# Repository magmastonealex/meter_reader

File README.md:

meter_reader
====

This is an open-hardware design for a magnetic gas / water meter "reader" or "snooper". It contains a magnetometer and microcontroller, and can measure the rotations of a water meter or oscillations of the bellows in a gas meter to fairly accurately track consumption of both natural gas and water.

The device communicates externally using CAN, accepting configuration and reporting sensor values.

Schematics and PCB design are in the root of this repository. I have built a few devices, but would not consider the hardware to be "fully qualified" yet - I still need to do some transient testing and measure power supplies and signal integrity. I'd also still like to find a more available magnetometer - MLX3094RLD is _barely_ available and a bit annoying to solder.

Firmware in `firmware/` is Rust code targetting the MSPM0G3107 on the board. I _think_ this is the first working example of MSPM0 CAN access in Rust on the internet :) It requires modifications to the mspm0-data crate which I have in a branch here: https://github.com/magmastonealex/mspm0-data - there is an open PR upstream where smarter people than I are figuring out a better way to do this.

The firmware right now is just bringing up various peripherals to prove they work - the code is very, very ugly, requiring a lot of cleanup, and doesn't really "do" anything yet.

More to come, including a blog post detailing assembly, development, and setup

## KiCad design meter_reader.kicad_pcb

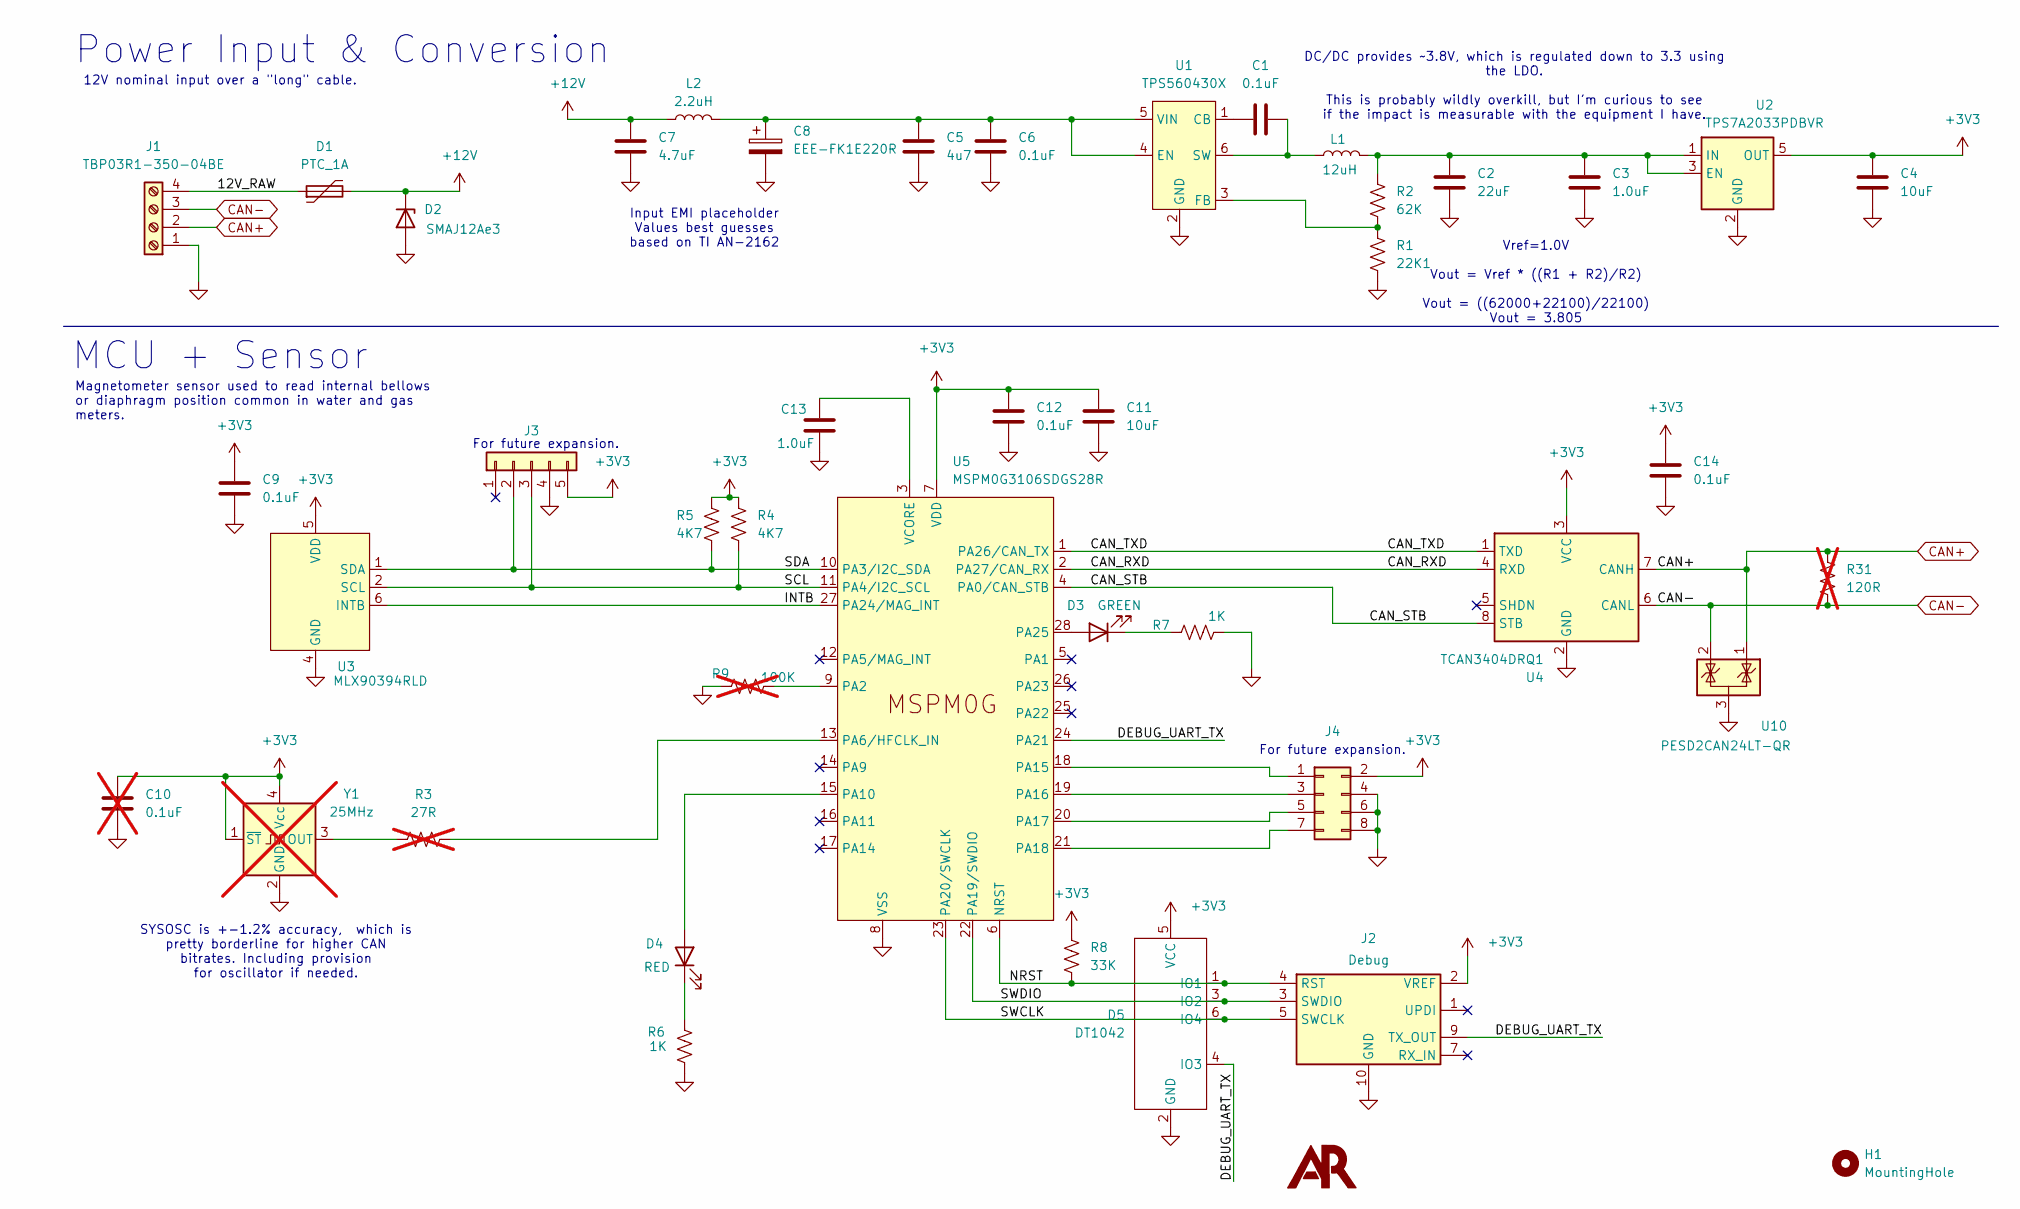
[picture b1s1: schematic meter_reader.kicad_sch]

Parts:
C1, C9: 0.1uF; C_0402_1005Metric
C2: 22uF; C_0805_2012Metric_Pad1.18x1.45mm_HandSolder
C3, C13: 1.0uF; C_0805_2012Metric_Pad1.18x1.45mm_HandSolder
C4, C11: 10uF; C_0805_2012Metric_Pad1.18x1.45mm_HandSolder
C5: 4u7; C_1206_3216Metric
C6, C12, C14: 0.1uF; C_0805_2012Metric_Pad1.18x1.45mm_HandSolder
C7: 4.7uF; C_1206_3216Metric
C8: EEE-FK1E220R; CP_Elec_5x5.8
C10: 0.1uF; C_0805_2012Metric_Pad1.18x1.45mm_HandSolder; not fitted
D1: PTC_1A; Fuse_1812
D2: SMAJ12Ae3; D_SMA
D3: GREEN; LED_0805_2012Metric_Pad1.15x1.40mm_HandSolder
D4: RED; LED_0805_2012Metric_Pad1.15x1.40mm_HandSolder
D5: DT1042; SOT-26
H1: MountingHole; MountingHole_2.2mm_M2
J1: TBP03R1-350-04BE; SameSky_TPB03R1-350-04BE
J2: Debug; Tag-Connect_TC2050-IDC-NL_2x05_P1.27mm_Vertical
J3: EXPAND; PinHeader_1x05_P2.54mm_Vertical
J4: Conn_02x04_Odd_Even; PinHeader_2x04_P2.54mm_Vertical
L1: 12uH; Bourns_SRR6038
L2: 2.2uH; L_1008_2520Metric
R1: 22K1; R_0805_2012Metric_Pad1.20x1.40mm_HandSolder
R2: 62K; R_0805_2012Metric_Pad1.20x1.40mm_HandSolder
R3: 27R; R_0603_1608Metric_Pad0.98x0.95mm_HandSolder; not fitted
R4, R5: 4K7; R_0805_2012Metric_Pad1.20x1.40mm_HandSolder
R6, R7: 1K; R_0805_2012Metric_Pad1.20x1.40mm_HandSolder
R8: 33K; R_0805_2012Metric_Pad1.20x1.40mm_HandSolder
R9: 100K; R_0805_2012Metric_Pad1.20x1.40mm_HandSolder; not fitted
R31: 120R; R_1210_3225Metric; not fitted
REF1: Touchmark_small
U1: TPS560430X; SOT-23-6
U2: TPS7A2033PDBVR; SOT-23-5
U3: MLX90394RLD; UTDFN-6-1EP_2x1.5mm_P0.5mm_EP0.8x0.8mm
U4: TCAN3404DRQ1; SOIC-8_3.9x4.9mm_P1.27mm
U5: MSPM0G3106SDGS28R; VSSOP-28_3x7.1mm_P0.5mm
U10: PESD2CAN24LT-QR; SOT-23
Y1: 25MHz; Oscillator_SMD_SeikoEpson_SG210-4Pin_2.5x2.0mm; not fitted

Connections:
+3V3: C4.1, C9.2, C10.1, C11.1, C12.1, C14.1, D5.5 (VCC), J2.2 (VREF), J3.5, J4.2, R4.2, R5.2, R8.1, U2.5 (OUT), U3.5 (VDD), U4.3 (VCC), U5.7 (VDD), Y1.1 (~ST), Y1.4 (Vcc)
+12V: C7.1, D1.2, D2.1 (K), L2.1
/12V_RAW: D1.1, J1.4
/CAN_RXD: U4.4 (RXD), U5.2 (PA27/CAN_RX)
/CAN_STB: U4.8 (STB), U5.4 (PA0/CAN_STB)
/CAN_TXD: U4.1 (TXD), U5.1 (PA26/CAN_TX)
/DEBUG_UART_TX: D5.4 (IO3), J2.9 (TX_OUT), U5.24 (PA21)
/INTB: U3.6 (INTB), U5.27 (PA24/MAG_INT)
/NRST: D5.1 (IO1), J2.4 (RST), R8.2, U5.6 (NRST)
/SCL: J3.3, R4.1, U3.2 (SCL), U5.11 (PA4/I2C_SCL)
/SDA: J3.2, R5.1, U3.1 (SDA), U5.10 (PA3/I2C_SDA)
/SWCLK: D5.6 (IO4), J2.5 (SWCLK), U5.23 (PA20/SWCLK)
/SWDIO: D5.3 (IO2), J2.3 (SWDIO), U5.22 (PA19/SWDIO)
CAN+: J1.2, R31.1, U4.7 (CANH), U10.1 (K)
CAN-: J1.3, R31.2, U4.6 (CANL), U10.2 (K)
GND: C2.2, C3.2, C4.2, C5.2, C6.2, C7.2, C8.2, C9.1, C10.2, C11.2, C12.2, C13.2, C14.2, D2.2 (A), D5.2 (GND), J1.1, J2.6 (GND), J2.8 (GND), J2.10 (GND), J3.4, J4.4, J4.6, J4.8, R1.2, R6.2, R7.2, R9.1, U1.2 (GND), U2.2 (GND), U3.3 (GND), U3.4 (GND), U4.2 (GND), U5.8 (VSS), U10.3 (A), Y1.2 (GND)
unnamed: D3.2 (A), U5.28 (PA25)
unnamed: D3.1 (K), R7.1
unnamed: D4.2 (A), U5.15 (PA10)
unnamed: D4.1 (K), R6.1
unnamed: J4.1, U5.18 (PA15)
unnamed: J4.3, U5.19 (PA16)
unnamed: J4.5, U5.20 (PA17)
unnamed: J4.7, U5.21 (PA18)
unnamed: C1.1, U1.1 (CB)
unnamed: C5.1, C6.1, C8.1, L2.2, U1.4 (EN), U1.5 (VIN)
unnamed: R1.1, R2.2, U1.3 (FB)
unnamed: C1.2, L1.1, U1.6 (SW)
unnamed: C2.1, C3.1, L1.2, R2.1, U2.1 (IN), U2.3 (EN)
unnamed: R9.2, U5.9 (PA2)
unnamed: R3.1, U5.13 (PA6/HFCLK_IN)
unnamed: C13.1, U5.3 (VCORE)
unnamed: R3.2, Y1.3 (OUT)

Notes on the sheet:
SYSOSC is +-1.2% accuracy, which is pretty borderline for higher CAN bitrates. Including provision for oscillator if needed.
12V nominal input over a "long" cable.
DC/DC provides ~3.8V, which is regulated down to 3.3 using the LDO. This is probably wildly overkill, but I'm curious to see if the impact is measurable with the equipment I have.
Power Input & Conversion
Input EMI placeholder Values best guesses based on TI AN-2162
For future expansion.
Magnetometer sensor used to read internal bellows or diaphragm position common in water and gas meters.
Vref=1.0V Vout = Vref * ((R1 + R2)/R2) Vout = ((62000+22100)/22100) Vout = 3.805
MCU + Sensor

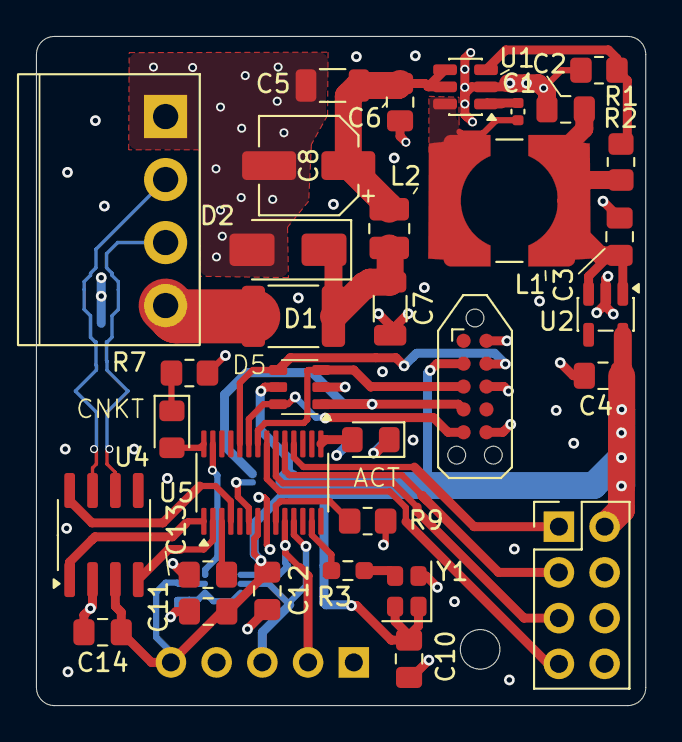
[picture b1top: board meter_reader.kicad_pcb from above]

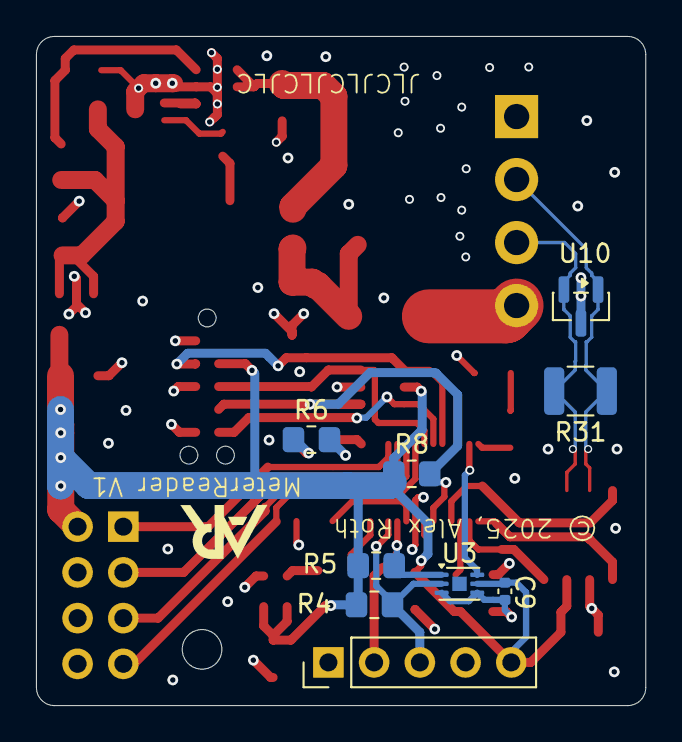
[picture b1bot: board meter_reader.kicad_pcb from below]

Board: 4 copper layers, 33.8 x 37.2 mm, 44 parts (10 on the bottom side), 33 nets.

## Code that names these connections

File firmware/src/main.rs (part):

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#[embassy_executor::main]
async fn main(spawner: Spawner) -> ! {
    let periph = embassy_mspm0::init(Default::default());
    let mut led_output = Output::new(periph.PA25, embassy_mspm0::gpio::Level::Low);
    let mut led_output_2 = Output::new(periph.PA10, embassy_mspm0::gpio::Level::High);
    let mut mlx_drdy = Input::new(periph.PA24, embassy_mspm0::gpio::Pull::Up);
    let canstb = Output::new(periph.PA0, embassy_mspm0::gpio::Level::Low);

    // Hack: Set up HFXT with the 25MHz oscillator
    // We'll use this for clocking the CAN peripheral
    // PA6 - PINCM11. Pin function 6 is HFCLK_IN.
    embassy_mspm0::pac::IOMUX.pincm(10).modify(|w| {
        w.set_pf(6);
        w.set_inena(true);
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    // Configure UART first - we will use it in our panic handler.
    let mut config = embassy_mspm0::uart::Config::default();
    config.baudrate = 115200;
    let mut uart = UartTx::new_blocking(periph.UART2, periph.PA21, config).unwrap();

    uart.blocking_write("hello\r\n".as_bytes()).unwrap();


    let mut mcan_config = can::Config::default();
    mcan_config.timing = CanTimings { brp: 1, sjw: 30, ntseg1: 219, ntseg2: 30 };
    let candriver = can::Can::new_async(periph.CANFD0, periph.PA27, periph.PA26, Irqs, mcan_config).unwrap();
    let (tx, mut rx, status) = candriver.split();

    spawner.spawn(transmitter_mux(tx, OUTBOUND.dyn_receiver()).unwrap());
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    // Initialize i2c.
    let mut cfg = i2c::Config::default();
    cfg.bus_speed = i2c::BusSpeed::FastMode;
    let mut i2cinter = match i2c::I2c::new_async(periph.I2C1, periph.PA4, periph.PA3, Irqs, cfg) {
        Ok(drv) => drv,
        Err(e) => {
            error!("i2c config error: {}", e);
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
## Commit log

2025-12-17 Project start
2025-12-17 Schematic completed, starting on placement
2025-12-17 placement continues
2025-12-20 Add breakout for backup magnetometer, add IO pin breakout, finish placement
2025-12-21 Meter reader V1 (probably) ready for fabrication
2025-12-22 Tidy up before mfg release
2026-01-03 Add firmware start point
2026-01-03 cargo config with toolchain
2026-01-03 Added embassy-executor (3K overhead)
2026-01-03 defmt and UART seem to be working as expected
2026-01-04 temp
2026-01-08 working on actual board
2026-01-09 CAN peripheral is initialized, but not 100% reliably. Need to figure out a proper reset path.
2026-01-09 Don't reset the CAN peripheral. This causes misbehaviour
2026-01-10 MCAN peripheral is functional, if a bit awkward to use
2026-01-10 Add notes to schematic from bringup
2026-01-10 Get ready for first publish
2026-01-11 Finally figure out why MCAN doesn't initialize on all boots
2026-01-11 Start on somewhat reasonable driver for CAN
2026-01-13 Temp - redirect to local embassy
2026-01-14 rip out all the working CAN code, starting to move it upstream.
2026-01-16 Can send and receive frames again
2026-02-01 update with new async support from CAn driver
2026-02-01 magnetometer is working with a slightly crappy driver
2026-02-03 Try a slightly sketchy flash program operation?
2026-02-04 Minimal flash driver is working. Now to decide if we want to implement the embedded-storage traits or DIY a flash layer
2026-02-06 Finish flash driver, add sequential-storage, some minor magnetometer improvements
2026-02-06 MLX readings work - bug in i2c driver identified with lack of repeated starts
2026-02-06 Have MLX driver take drdy pin, use it for triggering data retrieval.
2026-02-07 feature complete, in theory. Still lots and lots to test.
2026-02-07 add reset functionality
2026-02-07 Fixup CAN addressing. It works!
2026-02-08 Fix reset timing with mlx. Fix up some protocol typos in main
2026-02-08 Work around broken i2c driver for nacked writes
2026-02-13 Tweak to use HFCLK input for better CAN clock accuracy
2026-02-15 Update counts for real deployment
2026-02-16 CLAUDE: Add host application for managing and configuring devices
2026-02-16 Add temperature reporting with embassy hack

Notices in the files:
meter_reader.kicad_pcb:
© 2025, Alex Roth
